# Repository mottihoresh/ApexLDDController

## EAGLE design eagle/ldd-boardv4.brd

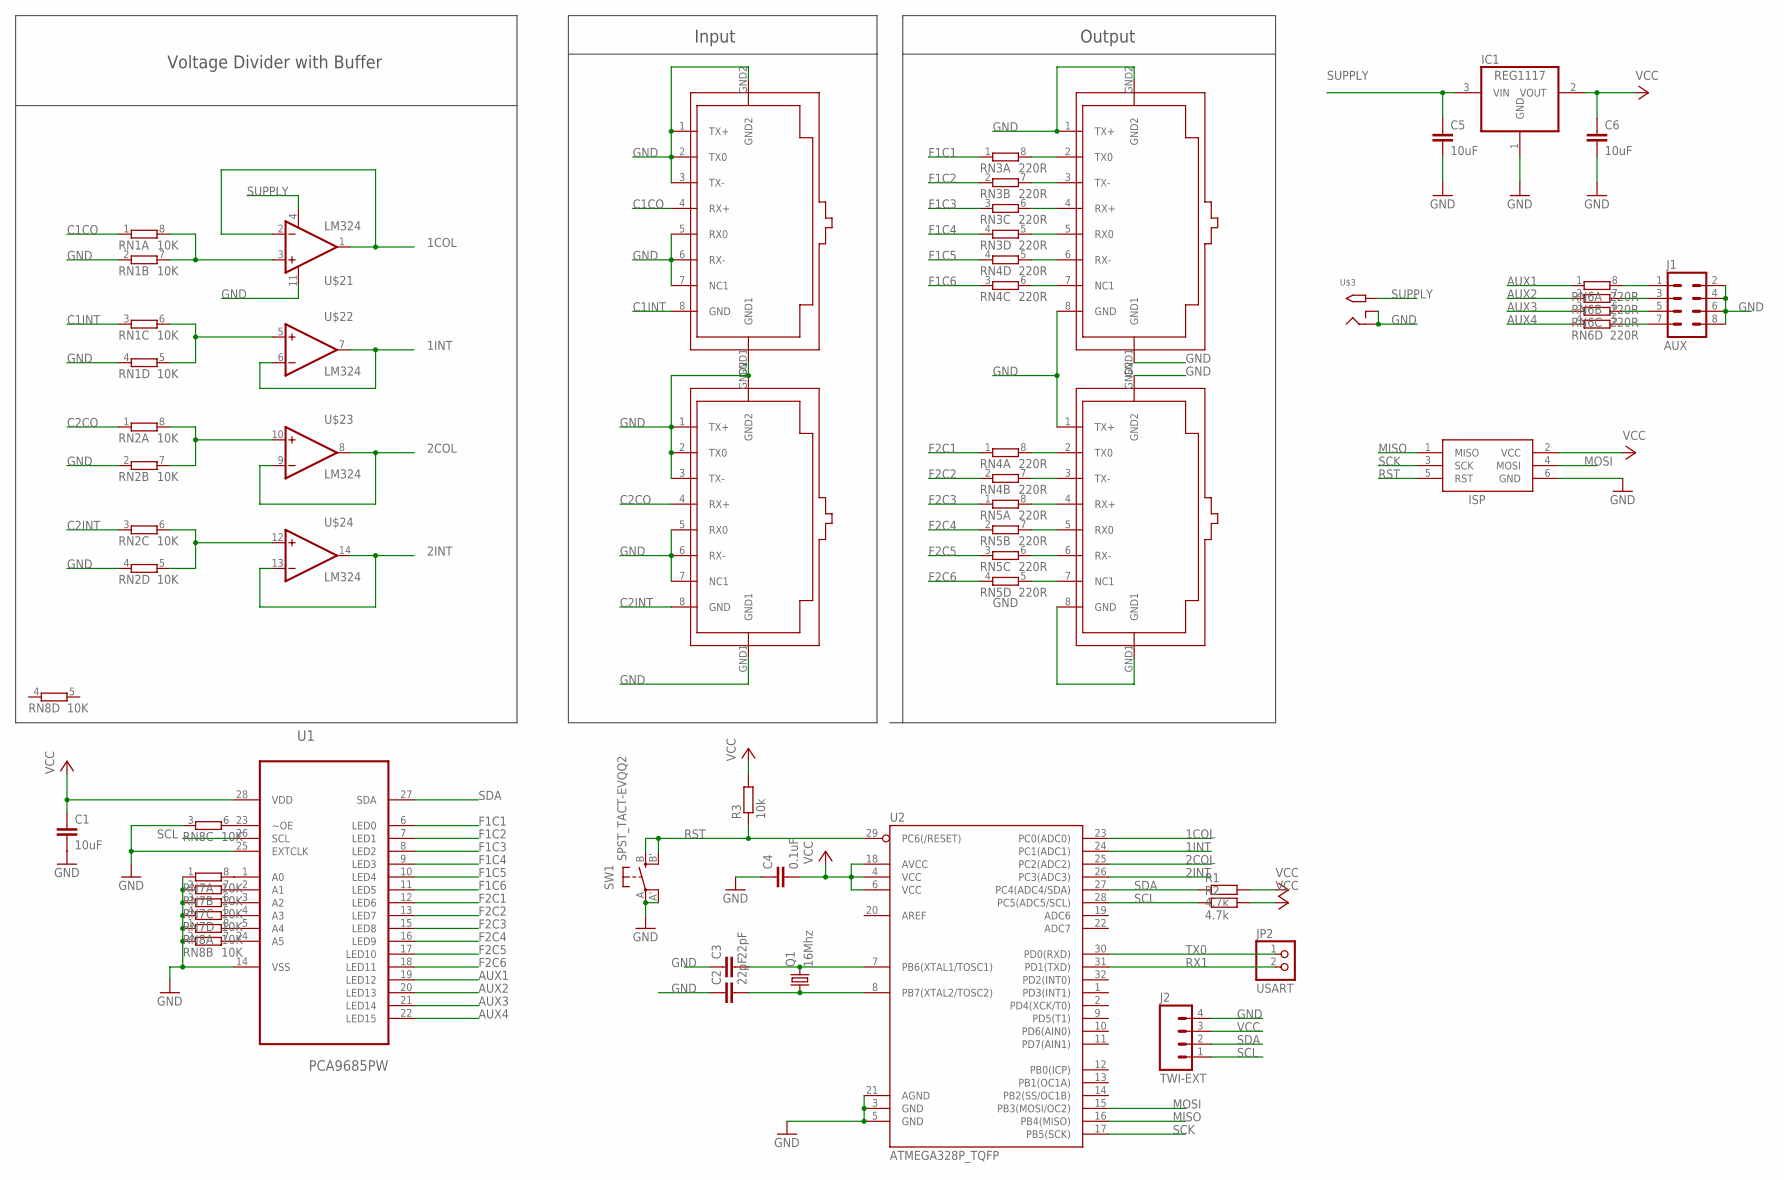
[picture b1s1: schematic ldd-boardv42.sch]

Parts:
C1, C5, C6: 10uF; C0805K; MPN GRT21BR61E106KE13L
C2, C3: 22pF; C0805K; MPN 04025A220JAT2A
C4: 0.1uF; C0805K; MPN 0603YC104K4Z2A
IC1: REG1117; SOT223
ISP: AVRISP-6; AVRISP
J1: AUX; 2X4
J2: TWI-EXT; 1X04
JP2: USART; 1X02
Q1: 16Mhz; HC49UP
R1, R2: 4.7k; R0805; MPN CRCW08054K70JNEA
R3: 10k; R0805; MPN TNPW080510K0DEEA
RN1, RN2: 10K; EXBV8V
RN3, RN4, RN5, RN6: 220R; EXBV8V
RN7, RN8: 10K; EXB38V
SW1: SPST_TACT-EVQQ2; EVQ-Q2
U1: PCA9685PW; SOP65P640X110-28N
U2: ATMEGA328P_TQFP; TQFP32-08
U$1, U$4, U$5, U$6: RJ45-TRAFO
U$2: LM324; SOIC-14
U$3: 2.1MMJACKTHM; PJ-102A

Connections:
1COL: U2.23 (PC0(ADC0)), U$2.1 (OUT), U$2.2 (-IN)
1INT: U2.24 (PC1(ADC1)), U$2.6 (-IN), U$2.7 (OUT)
2COL: U2.25 (PC2(ADC2)), U$2.8 (OUT), U$2.9 (-IN)
2INT: U2.26 (PC3(ADC3)), U$2.13 (-IN), U$2.14 (OUT)
AUX1: RN6.1, U1.19 (LED12)
AUX2: RN6.2 (1), U1.20 (LED13)
AUX3: RN6.3 (1), U1.21 (LED14)
AUX4: RN6.4 (1), U1.22 (LED15)
C1CO: RN1.1, U$6.4 (RX+)
C1INT: RN1.3 (1), U$6.8 (GND)
C2CO: RN2.1, U$5.4 (RX+)
C2INT: RN2.3 (1), U$5.8 (GND)
F1C1: RN3.1, U1.6 (LED0)
F1C2: RN3.2 (1), U1.7 (LED1)
F1C3: RN3.3 (1), U1.8 (LED2)
F1C4: RN3.4 (1), U1.9 (LED3)
F1C5: RN4.4 (1), U1.10 (LED4)
F1C6: RN4.3 (1), U1.11 (LED5)
F2C1: RN4.1, U1.12 (LED6)
F2C2: RN4.2 (1), U1.13 (LED7)
F2C3: RN5.1, U1.15 (LED8)
F2C4: RN5.2 (1), U1.16 (LED9)
F2C5: RN5.3 (1), U1.17 (LED10)
F2C6: RN5.4 (1), U1.18 (LED11)
GND: C1.2, C2.1, C3.1, C4.1, C5.2, C6.2, IC1.1 (GND), ISP.6 (GND), J1.2, J1.4, J1.6, J1.8, J2.4, RN1.2 (1), RN1.4 (1), RN2.2 (1), RN2.4 (1), RN7.1, RN7.2 (1), RN7.3 (1), RN7.4 (1), RN8.1, RN8.2 (1), RN8.3 (1), SW1.A, SW1.A' (P1), U1.14 (VSS), U1.25 (EXTCLK), U2.3 (GND), U2.5 (GND), U2.21 (AGND), U$1.1 (TX+), U$1.8 (GND), U$1.GND1, U$1.GND2, U$2.11 (V-), U$3.RING, U$3.RING_SW, U$4.1 (TX+), U$4.8 (GND), U$4.GND1, U$4.GND2, U$5.1 (TX+), U$5.2 (TX0), U$5.3 (TX-), U$5.5 (RX0), U$5.6 (RX-), U$5.7 (NC1), U$5.GND1, U$5.GND2, U$6.1 (TX+), U$6.2 (TX0), U$6.3 (TX-), U$6.5 (RX0), U$6.6 (RX-), U$6.7 (NC1), U$6.GND1, U$6.GND2
MISO: ISP.1 (MISO), U2.16 (PB4(MISO))
MOSI: ISP.4 (MOSI), U2.15 (PB3(MOSI/OC2))
unnamed: RN1.7 (2), RN1.8 (2), U$2.3 (+IN)
unnamed: RN1.5 (2), RN1.6 (2), U$2.5 (+IN)
unnamed: J1.1, RN6.8 (2)
unnamed: RN4.6 (2), U$4.7 (NC1)
unnamed: RN2.7 (2), RN2.8 (2), U$2.10 (+IN)
unnamed: RN4.5 (2), U$4.6 (RX-)
unnamed: RN3.5 (2), U$4.5 (RX0)
unnamed: RN2.5 (2), RN2.6 (2), U$2.12 (+IN)
unnamed: RN3.6 (2), U$4.4 (RX+)
unnamed: RN3.7 (2), U$4.3 (TX-)
unnamed: RN3.8 (2), U$4.2 (TX0)
unnamed: J1.3, RN6.7 (2)
unnamed: J1.5, RN6.6 (2)
unnamed: J1.7, RN6.5 (2)
unnamed: RN7.8 (2), U1.1 (A0)
unnamed: RN7.7 (2), U1.2 (A1)
unnamed: RN7.6 (2), U1.3 (A2)
unnamed: RN7.5 (2), U1.4 (A3)
unnamed: RN8.8 (2), U1.5 (A4)
unnamed: RN4.7 (2), U$1.3 (TX-)
unnamed: RN4.8 (2), U$1.2 (TX0)
unnamed: RN5.8 (2), U$1.4 (RX+)
unnamed: RN5.7 (2), U$1.5 (RX0)
unnamed: RN5.6 (2), U$1.6 (RX-)
unnamed: RN5.5 (2), U$1.7 (NC1)
unnamed: RN8.7 (2), U1.24 (A5)
unnamed: C3.2, Q1.2, U2.7 (PB6(XTAL1/TOSC1))
unnamed: RN8.6 (2), U1.23 (~OE)
unnamed: C2.2, Q1.1, U2.8 (PB7(XTAL2/TOSC2))
RST: ISP.5 (RST), R3.1, SW1.B (S), SW1.B' (S1), U2.29 (PC6(/RESET))
RX1: JP2.2, U2.31 (PD1(TXD))
SCK: ISP.3 (SCK), U2.17 (PB5(SCK))
SCL: J2.1, R2.1, U1.26 (SCL), U2.28 (PC5(ADC5/SCL))
SDA: J2.2, R1.1, U1.27 (SDA), U2.27 (PC4(ADC4/SDA))
SUPPLY: C5.1, IC1.3 (VIN), U$2.4 (V+), U$3.TIP
TX0: JP2.1, U2.30 (PD0(RXD))
VCC: C1.1, C4.2, C6.1, IC1.2 (VOUT), ISP.2 (VCC), J2.3, R1.2, R2.2, R3.2, U1.28 (VDD), U2.4 (VCC), U2.6 (VCC), U2.18 (AVCC)

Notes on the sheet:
Voltage Divider with Buffer
Input
Output

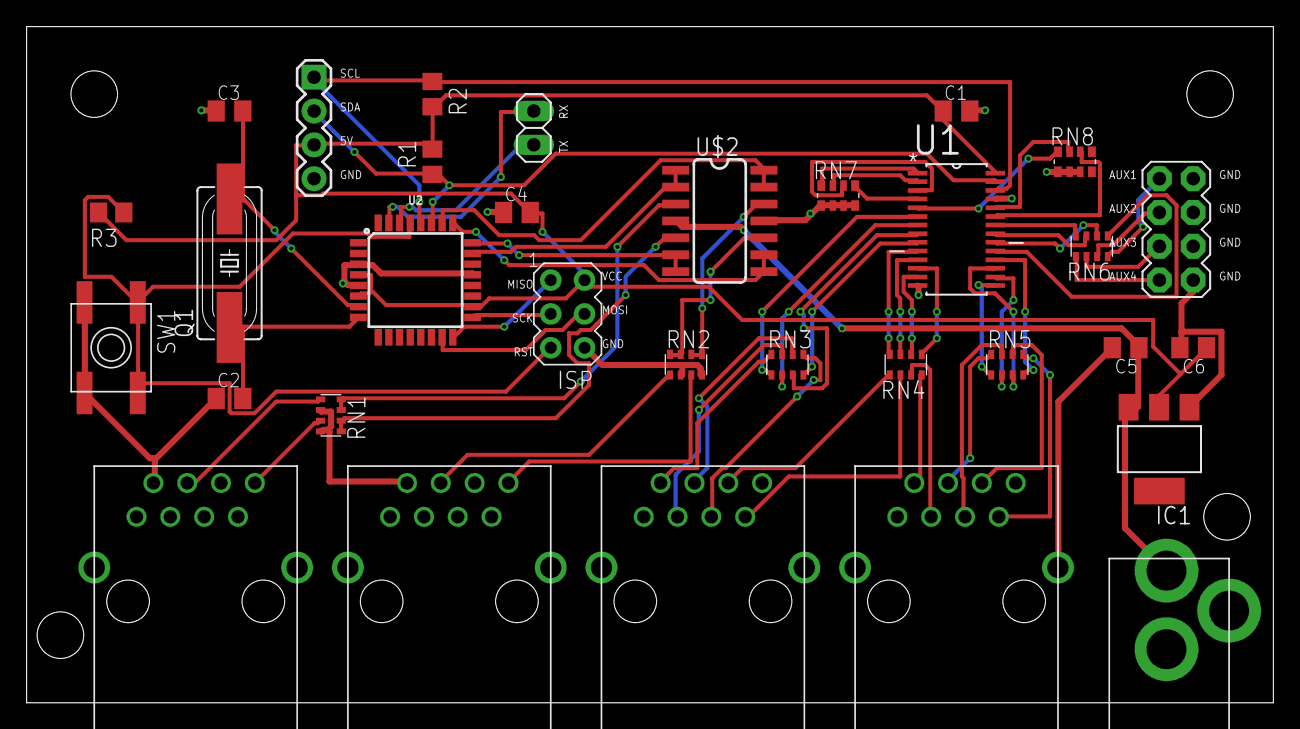
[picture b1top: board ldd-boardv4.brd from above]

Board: 2 copper layers, 93.7 x 50.8 mm, 32 parts (0 on the bottom side), 64 nets.

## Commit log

2017-11-06 updated display to add support for sd1306
2017-11-06 LedPuck struct and some helper functions
2017-11-17 added color presets
2017-11-17 light mapping calculations

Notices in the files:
parts and their libraries:
SparkFun-IC-Microcontroller: Licensing: Creative Commons ShareAlike 4.0 International - https://creativecommons.org/licenses/by-sa/4.0
